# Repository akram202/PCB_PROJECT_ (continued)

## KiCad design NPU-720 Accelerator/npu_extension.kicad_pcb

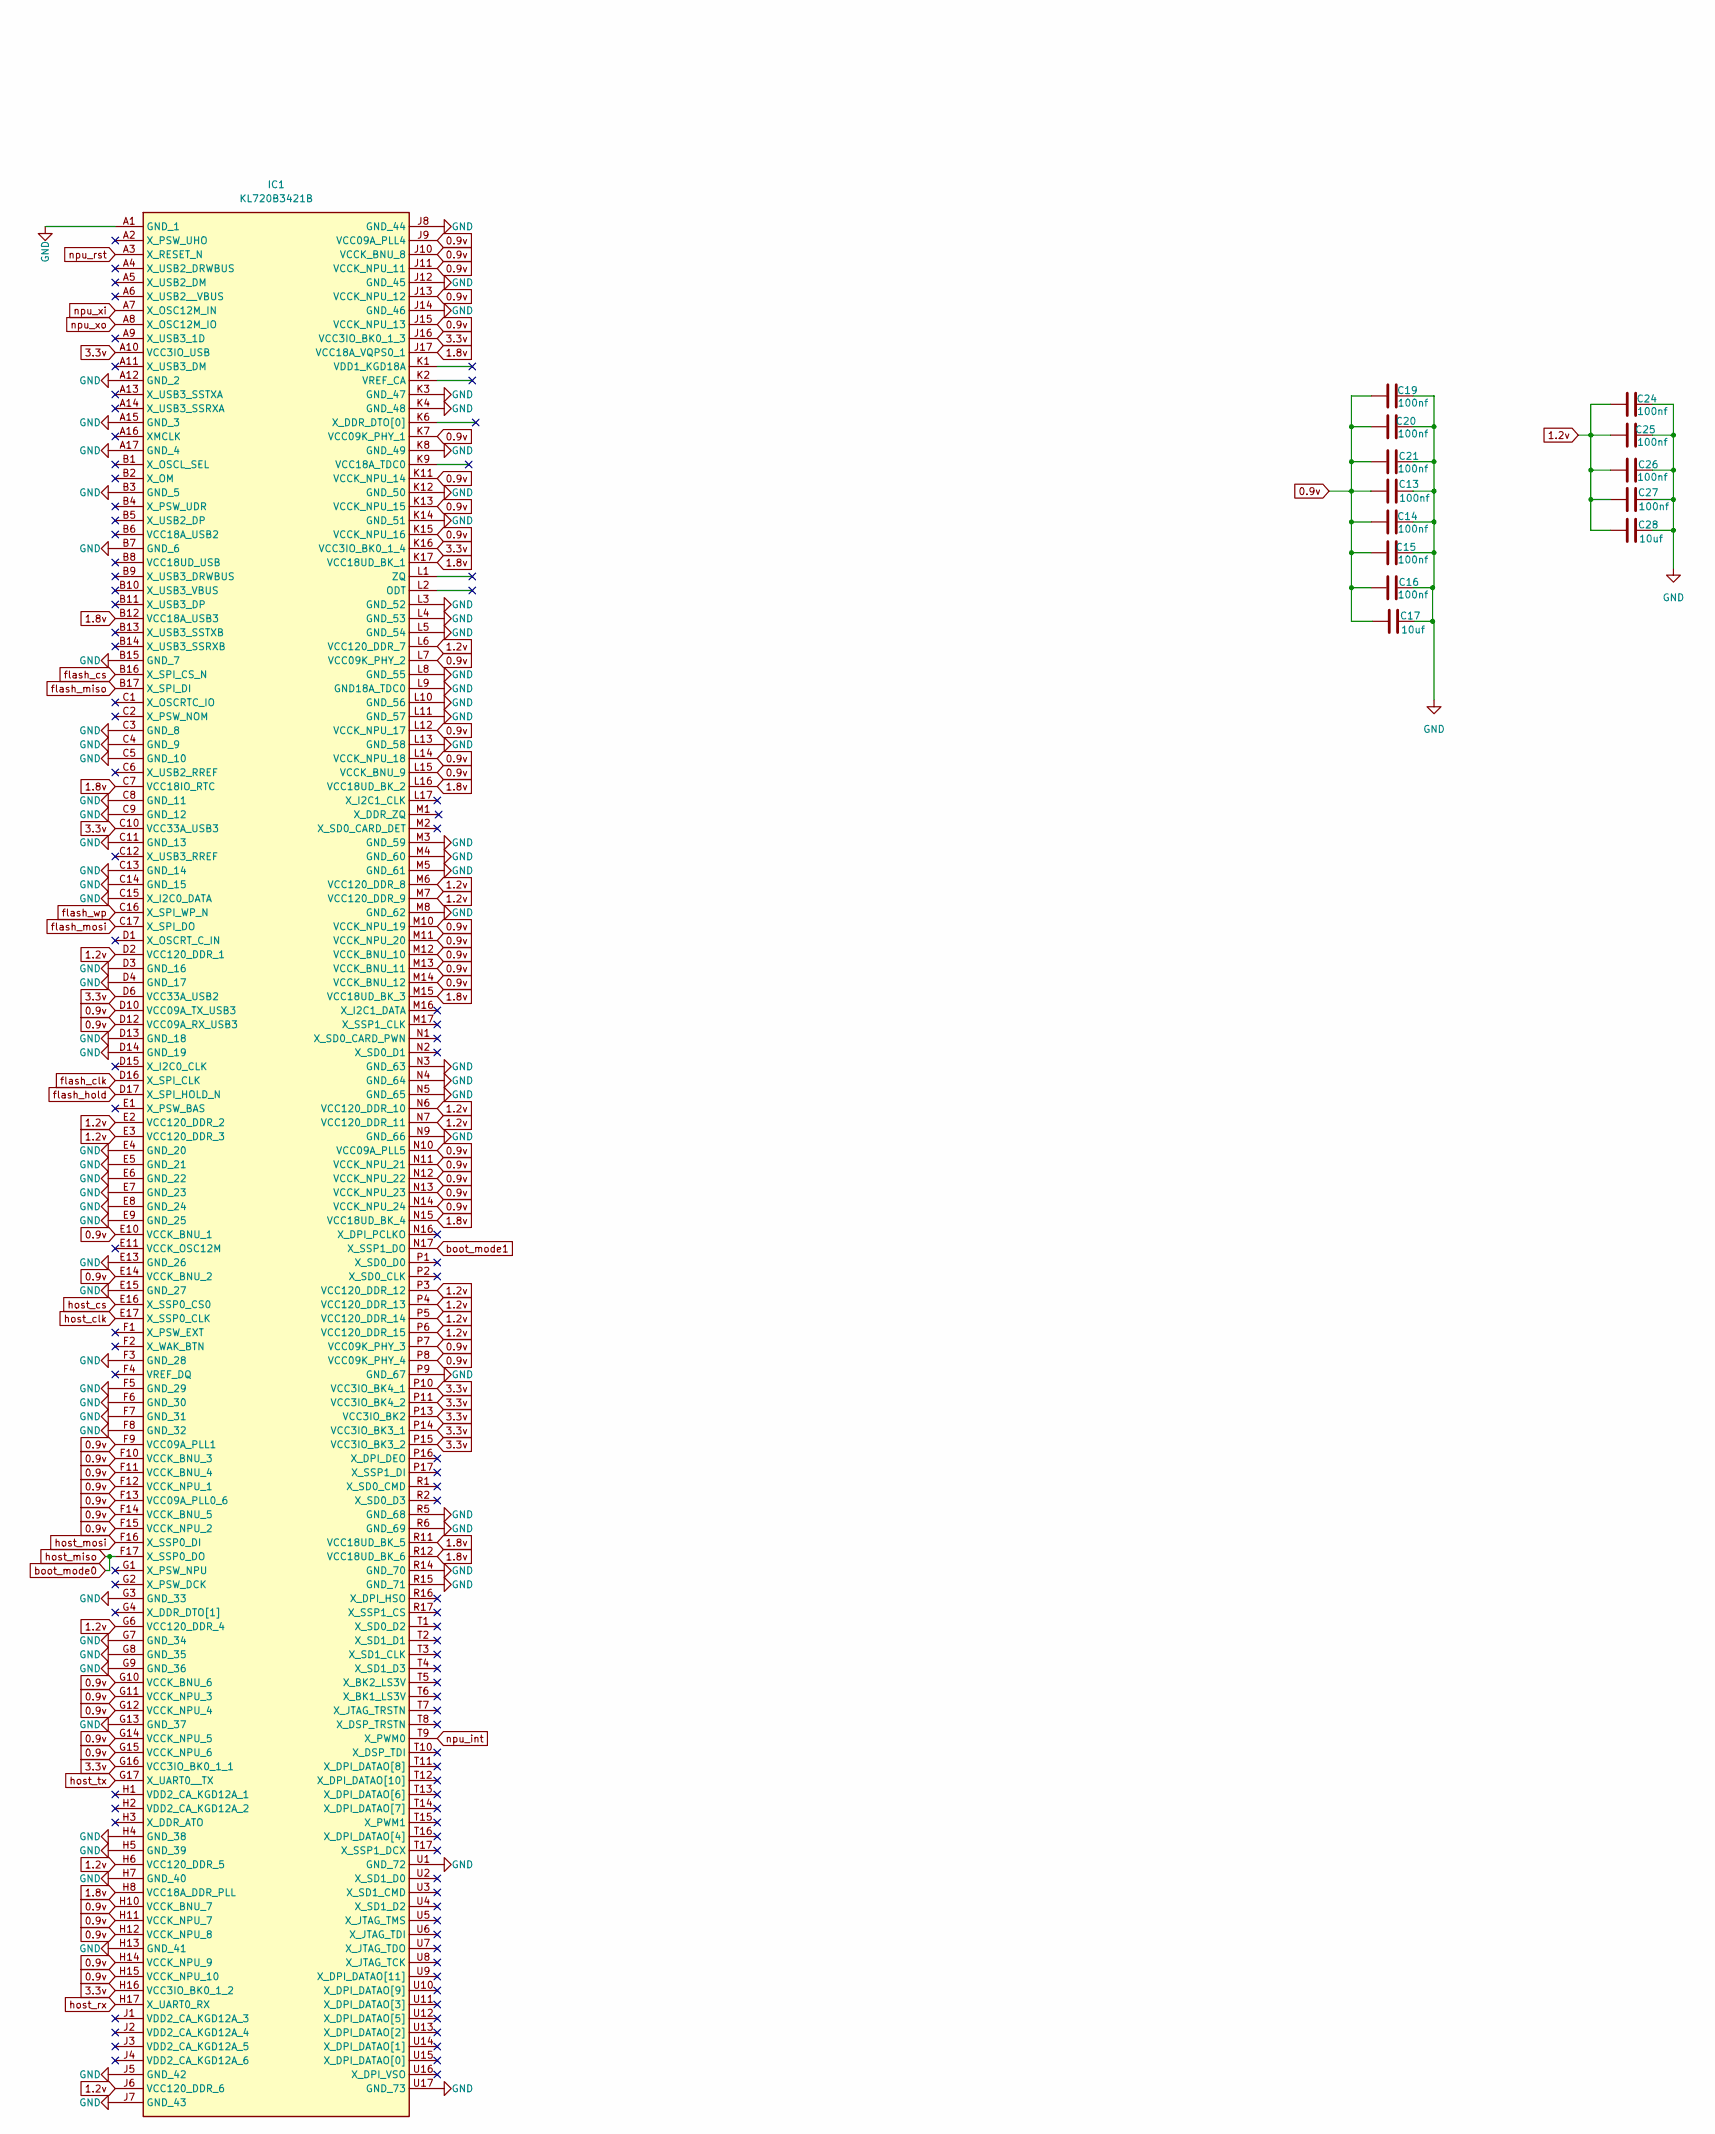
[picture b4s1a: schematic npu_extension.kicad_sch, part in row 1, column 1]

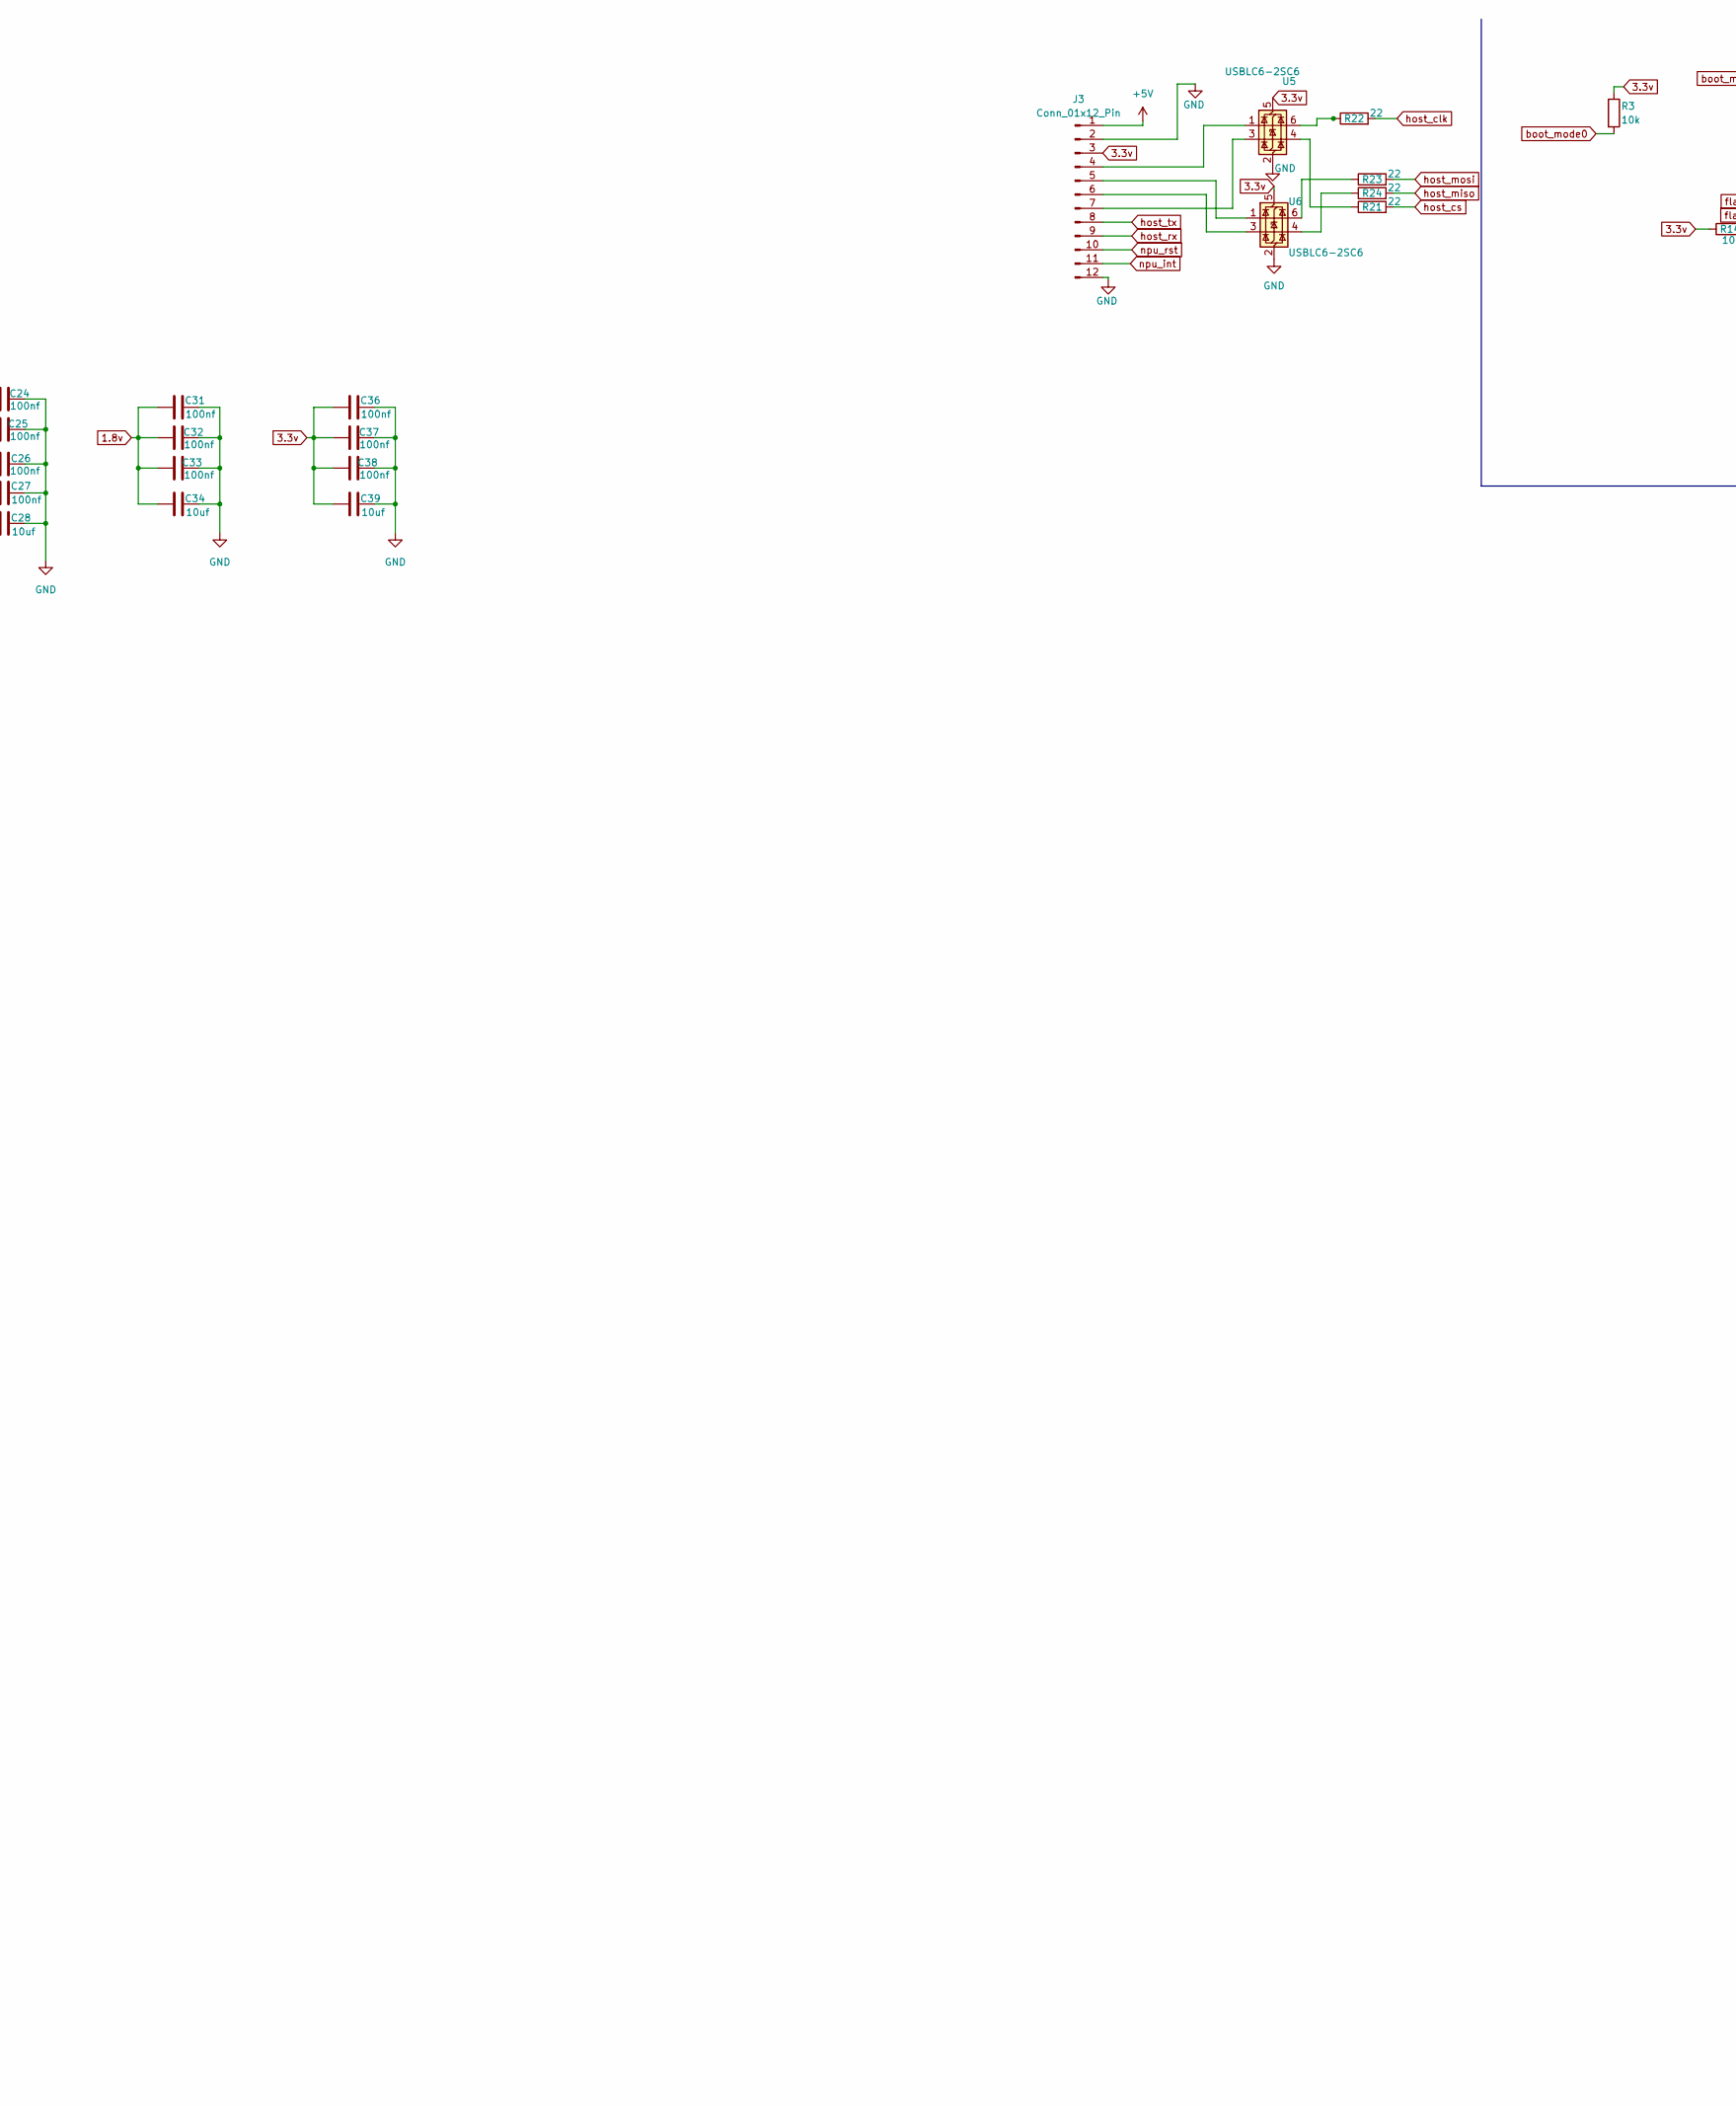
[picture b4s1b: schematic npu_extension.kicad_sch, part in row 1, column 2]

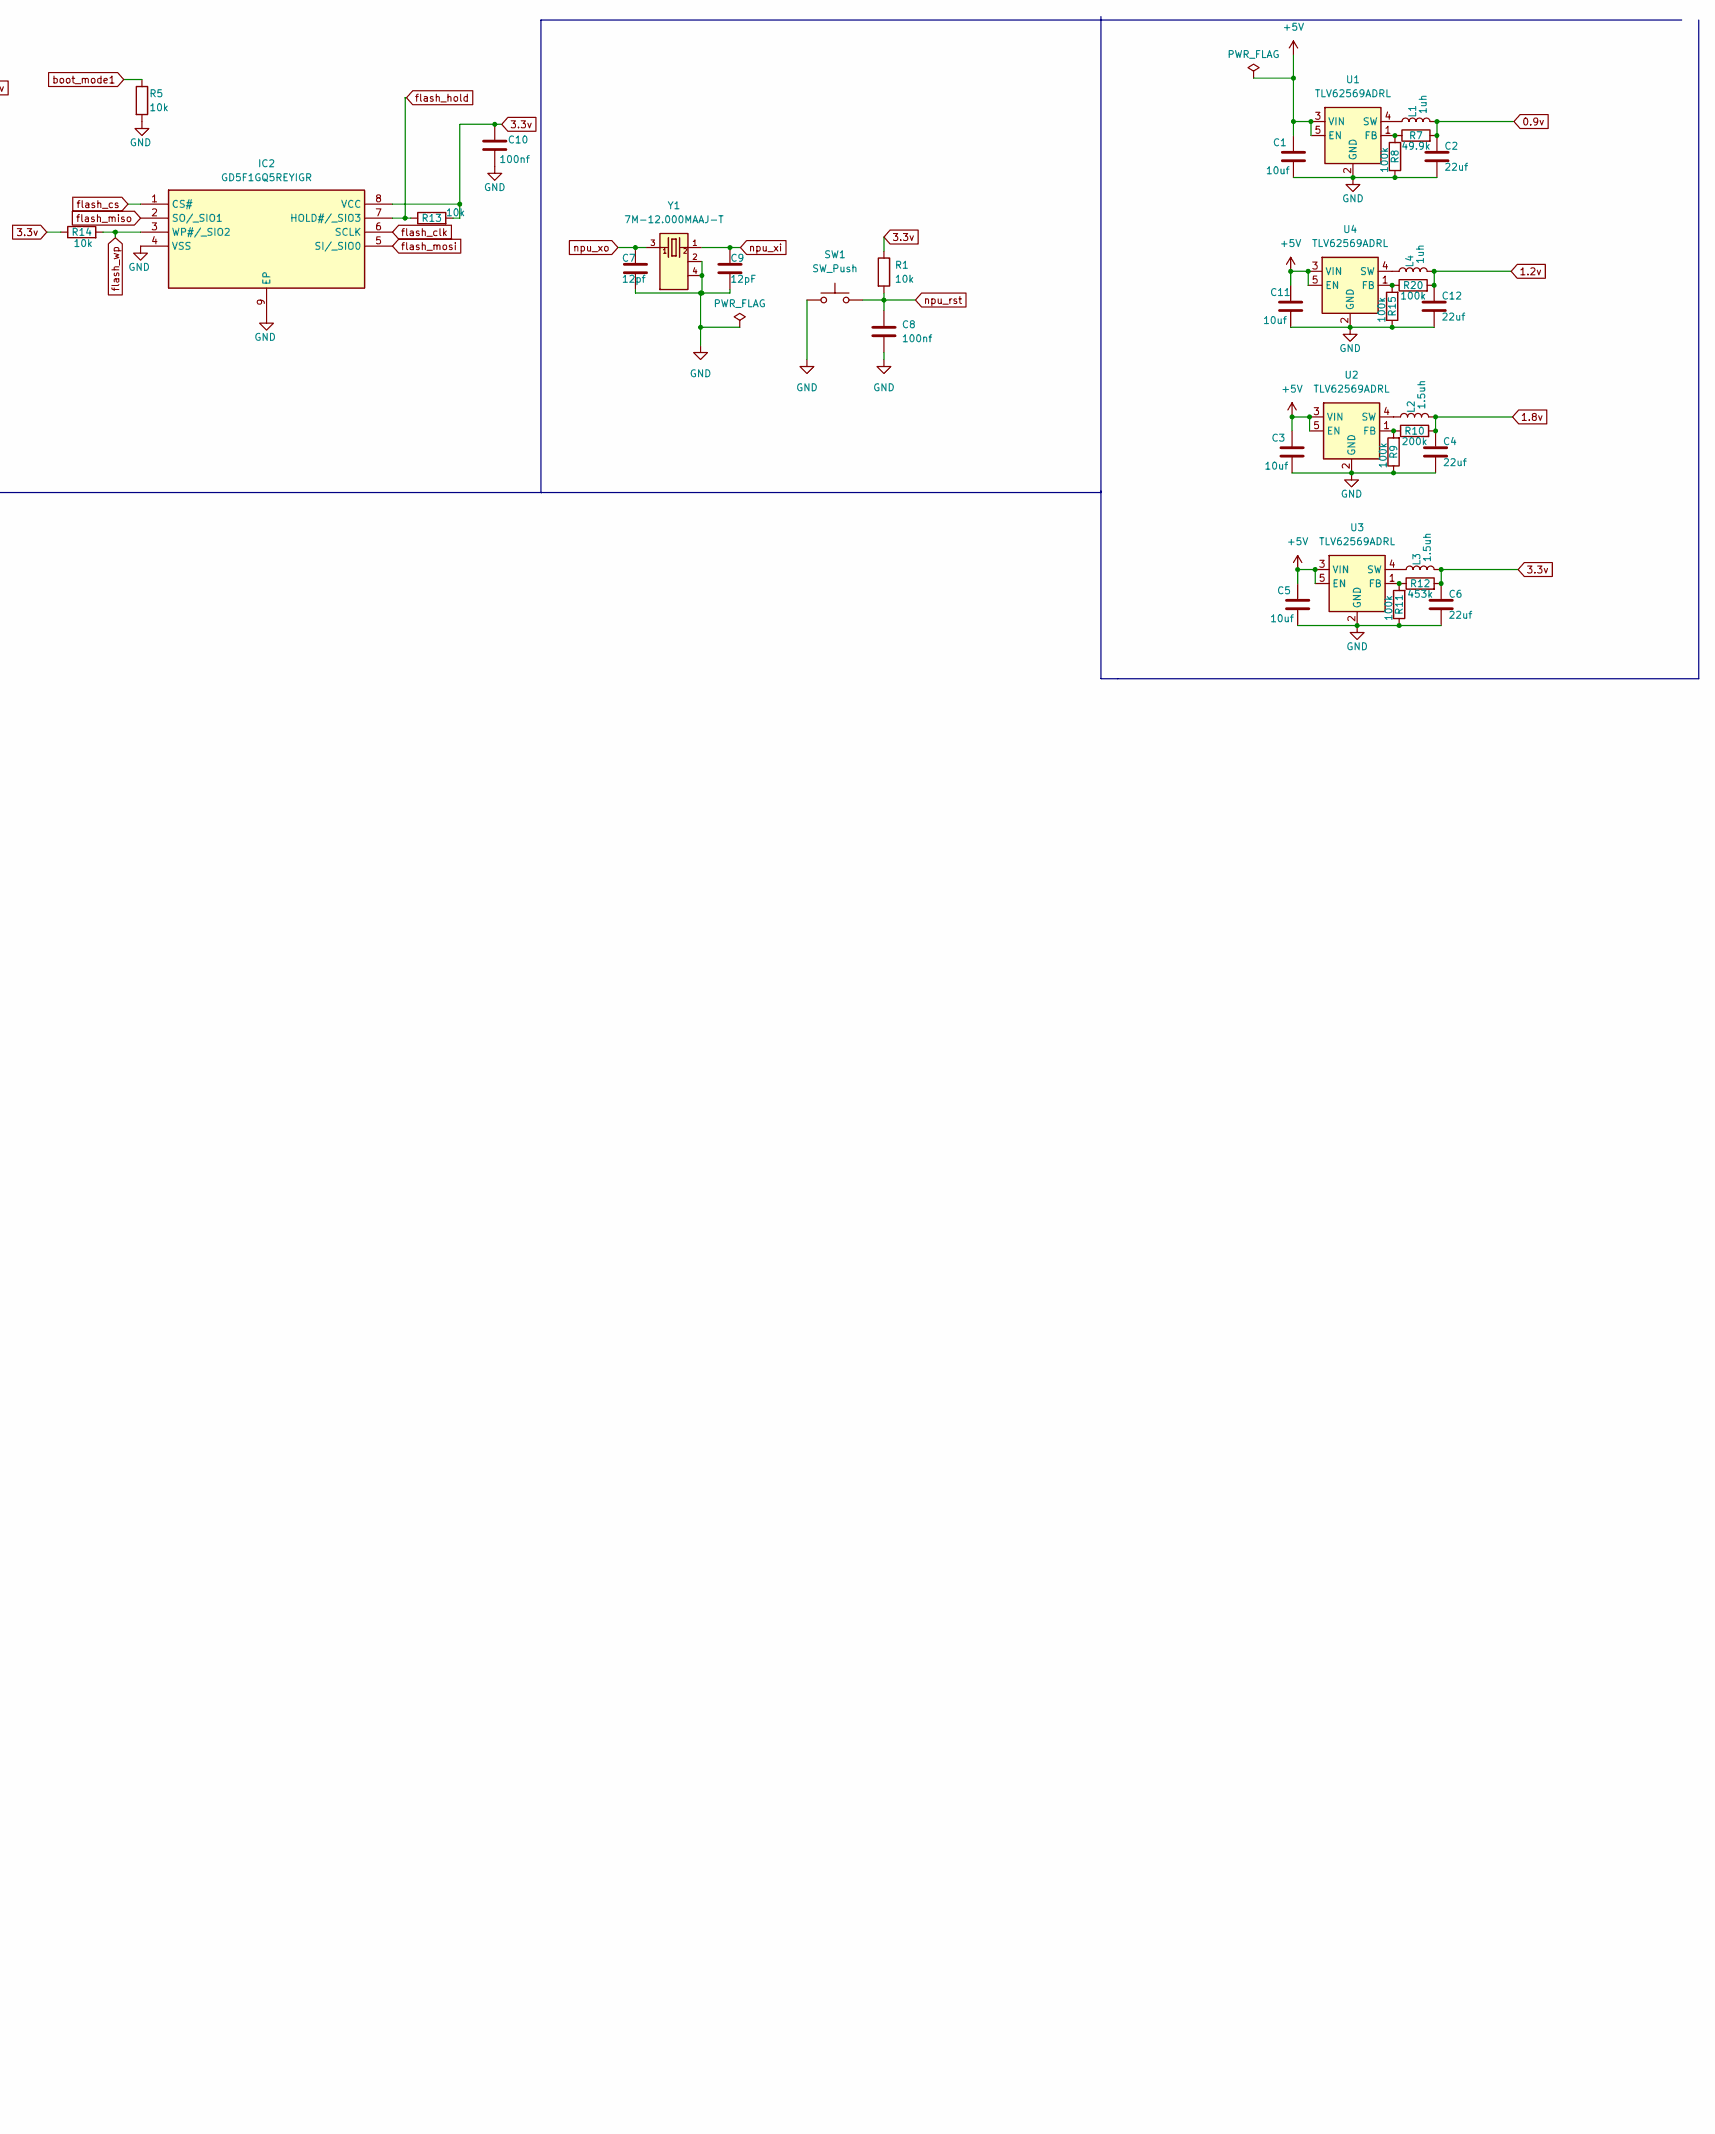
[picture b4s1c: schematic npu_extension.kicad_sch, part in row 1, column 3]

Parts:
C1, C3, C5, C11, C17, C28, C34, C39: 10uf; C_0805_2012Metric_Pad1.18x1.45mm_HandSolder
C2, C4, C6, C12: 22uf; C_0805_2012Metric_Pad1.18x1.45mm_HandSolder
C7: 12pf; C_0402_1005Metric_Pad0.74x0.62mm_HandSolder
C8, C10, C13, C14, C15, C16, C19, C20, C21, C24, C25, C26, C27, C31, C32, C33, C36, C37, C38: 100nf; C_0603_1608Metric_Pad1.08x0.95mm_HandSolder
C9: 12pF; C_0402_1005Metric_Pad0.74x0.62mm_HandSolder
IC1: KL720B3421B; BGA269C50P17X17_900X900X119; Manufacturer_Part_Number KL720B3421B; Mouser Part Number 827-KL720B3421B
IC2: GD5F1GQ5REYIGR; SON127P800X600X80-9N-D; Manufacturer_Part_Number GD5F1GQ5REYIGR
J3: Conn_01x12_Pin; JST_PH_S12B-PH-K_1x12_P2.00mm_Horizontal
L1, L4: 1uh; L_2512_6332Metric_Pad1.52x3.35mm_HandSolder
L2, L3: 1.5uh; L_2512_6332Metric_Pad1.52x3.35mm_HandSolder
R1, R3, R5, R13, R14: 10k; R_0603_1608Metric_Pad0.98x0.95mm_HandSolder
R7: 49.9k; R_0805_2012Metric_Pad1.20x1.40mm_HandSolder
R8, R9, R11, R15: 100k; R_0603_1608Metric_Pad0.98x0.95mm_HandSolder
R10: 200k; R_0805_2012Metric_Pad1.20x1.40mm_HandSolder
R12: 453k; R_0805_2012Metric_Pad1.20x1.40mm_HandSolder
R20: 100k; R_0805_2012Metric_Pad1.20x1.40mm_HandSolder
R21, R22, R23, R24: 22; R_0402_1005Metric_Pad0.72x0.64mm_HandSolder
SW1: SW_Push; SW_SPST_PTS645Sx43SMTR92
U1, U2, U3, U4: TLV62569ADRL; SOT-563
U5, U6: USBLC6-2SC6; SOT-23-6
Y1: 7M-12.000MAAJ-T; Crystal_SMD_2520-4Pin_2.5x2.0mm

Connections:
0.9v: C2.1, C13.1, C14.1, C15.1, C16.1, C17.1, C19.1, C20.1, C21.1, IC1.D10 (VCC09A_TX_USB3), IC1.D12 (VCC09A_RX_USB3), IC1.E10 (VCCK_BNU_1), IC1.E14 (VCCK_BNU_2), IC1.F9 (VCC09A_PLL1), IC1.F10 (VCCK_BNU_3), IC1.F11 (VCCK_BNU_4), IC1.F12 (VCCK_NPU_1), IC1.F13 (VCC09A_PLL0_6), IC1.F14 (VCCK_BNU_5), IC1.F15 (VCCK_NPU_2), IC1.G10 (VCCK_BNU_6), IC1.G11 (VCCK_NPU_3), IC1.G12 (VCCK_NPU_4), IC1.G14 (VCCK_NPU_5), IC1.G15 (VCCK_NPU_6), IC1.H10 (VCCK_BNU_7), IC1.H11 (VCCK_NPU_7), IC1.H12 (VCCK_NPU_8), IC1.H14 (VCCK_NPU_9), IC1.H15 (VCCK_NPU_10), IC1.J9 (VCC09A_PLL4), IC1.J10 (VCCK_BNU_8), IC1.J11 (VCCK_NPU_11), IC1.J13 (VCCK_NPU_12), IC1.J15 (VCCK_NPU_13), IC1.K7 (VCC09K_PHY_1), IC1.K11 (VCCK_NPU_14), IC1.K13 (VCCK_NPU_15), IC1.K15 (VCCK_NPU_16), IC1.L7 (VCC09K_PHY_2), IC1.L12 (VCCK_NPU_17), IC1.L14 (VCCK_NPU_18), IC1.L15 (VCCK_BNU_9), IC1.M10 (VCCK_NPU_19), IC1.M11 (VCCK_NPU_20), IC1.M12 (VCCK_BNU_10), IC1.M13 (VCCK_BNU_11), IC1.M14 (VCCK_BNU_12), IC1.N10 (VCC09A_PLL5), IC1.N11 (VCCK_NPU_21), IC1.N12 (VCCK_NPU_22), IC1.N13 (VCCK_NPU_23), IC1.N14 (VCCK_NPU_24), IC1.P7 (VCC09K_PHY_3), IC1.P8 (VCC09K_PHY_4), L1.2, R7.2; also elsewhere on the board
1.2v: C12.1, C24.1, C25.1, C26.1, C27.1, C28.1, IC1.D2 (VCC120_DDR_1), IC1.E2 (VCC120_DDR_2), IC1.E3 (VCC120_DDR_3), IC1.G6 (VCC120_DDR_4), IC1.H6 (VCC120_DDR_5), IC1.J6 (VCC120_DDR_6), IC1.L6 (VCC120_DDR_7), IC1.M6 (VCC120_DDR_8), IC1.M7 (VCC120_DDR_9), IC1.N6 (VCC120_DDR_10), IC1.N7 (VCC120_DDR_11), IC1.P3 (VCC120_DDR_12), IC1.P4 (VCC120_DDR_13), IC1.P5 (VCC120_DDR_14), IC1.P6 (VCC120_DDR_15), L4.2, R20.2; also elsewhere on the board
1.8v: C4.1, C31.1, C32.1, C33.1, C34.1, IC1.B12 (VCC18A_USB3), IC1.C7 (VCC18IO_RTC), IC1.H8 (VCC18A_DDR_PLL), IC1.J17 (VCC18A_VQPS0_1), IC1.K17 (VCC18UD_BK_1), IC1.L16 (VCC18UD_BK_2), IC1.M15 (VCC18UD_BK_3), IC1.N15 (VCC18UD_BK_4), IC1.R11 (VCC18UD_BK_5), IC1.R12 (VCC18UD_BK_6), L2.2, R10.2; also elsewhere on the board
3.3v: C6.1, C10.1, C36.1, C37.1, C38.1, C39.1, IC1.A10 (VCC3IO_USB), IC1.C10 (VCC33A_USB3), IC1.D6 (VCC33A_USB2), IC1.G16 (VCC3IO_BK0_1_1), IC1.H16 (VCC3IO_BK0_1_2), IC1.J16 (VCC3IO_BK0_1_3), IC1.K16 (VCC3IO_BK0_1_4), IC1.P10 (VCC3IO_BK4_1), IC1.P11 (VCC3IO_BK4_2), IC1.P13 (VCC3IO_BK2), IC1.P14 (VCC3IO_BK3_1), IC1.P15 (VCC3IO_BK3_2), IC2.8 (VCC), J3.3, L3.2, R1.1, R3.1, R12.2, R13.2, R14.1, U5.5 (VBUS), U6.5 (VBUS); also elsewhere on the board
+5V: C1.1, C3.1, C5.1, C11.1, J3.1, U1.3 (VIN), U1.5 (EN), U2.3 (VIN), U2.5 (EN), U3.3 (VIN), U3.5 (EN), U4.3 (VIN), U4.5 (EN)
GND: C1.2, C2.2, C3.2, C4.2, C5.2, C6.2, C7.2, C8.2, C9.2, C10.2, C11.2, C12.2, C13.2, C14.2, C15.2, C16.2, C17.2, C19.2, C20.2, C21.2, C24.2, C25.2, C26.2, C27.2, C28.2, C31.2, C32.2, C33.2, C34.2, C36.2, C37.2, C38.2, C39.2, IC1.A1 (GND_1), IC1.A12 (GND_2), IC1.A15 (GND_3), IC1.A17 (GND_4), IC1.B3 (GND_5), IC1.B7 (GND_6), IC1.B15 (GND_7), IC1.C3 (GND_8), IC1.C4 (GND_9), IC1.C5 (GND_10), IC1.C8 (GND_11), IC1.C9 (GND_12), IC1.C11 (GND_13), IC1.C13 (GND_14), IC1.C14 (GND_15), IC1.C15 (X_I2C0_DATA), IC1.D3 (GND_16), IC1.D4 (GND_17), IC1.D13 (GND_18), IC1.D14 (GND_19), IC1.E4 (GND_20), IC1.E5 (GND_21), IC1.E6 (GND_22), IC1.E7 (GND_23), IC1.E8 (GND_24), IC1.E9 (GND_25), IC1.E13 (GND_26), IC1.E15 (GND_27), IC1.F3 (GND_28), IC1.F5 (GND_29), IC1.F6 (GND_30), IC1.F7 (GND_31), IC1.F8 (GND_32), IC1.G3 (GND_33), IC1.G7 (GND_34), IC1.G8 (GND_35), IC1.G9 (GND_36), IC1.G13 (GND_37), IC1.H4 (GND_38), IC1.H5 (GND_39), IC1.H7 (GND_40), IC1.H13 (GND_41), IC1.J5 (GND_42), IC1.J7 (GND_43), IC1.J8 (GND_44), IC1.J12 (GND_45), IC1.J14 (GND_46), IC1.K3 (GND_47), IC1.K4 (GND_48), IC1.K8 (GND_49), IC1.K12 (GND_50), IC1.K14 (GND_51), IC1.L3 (GND_52), IC1.L4 (GND_53), IC1.L5 (GND_54), IC1.L8 (GND_55), IC1.L9 (GND18A_TDC0), IC1.L10 (GND_56), IC1.L11 (GND_57), IC1.L13 (GND_58), IC1.M3 (GND_59), IC1.M4 (GND_60), IC1.M5 (GND_61), IC1.M8 (GND_62), IC1.N3 (GND_63), IC1.N4 (GND_64), IC1.N5 (GND_65), IC1.N9 (GND_66), IC1.P9 (GND_67), IC1.R5 (GND_68), IC1.R6 (GND_69), IC1.R14 (GND_70), IC1.R15 (GND_71), IC1.U1 (GND_72), IC1.U17 (GND_73), IC2.4 (VSS), IC2.9 (EP), J3.2, J3.12, R5.2, R8.1, R9.1, R11.1, R15.1, SW1.1, U1.2 (GND), U2.2 (GND), U3.2 (GND), U4.2 (GND), U5.2 (GND), U6.2 (GND), Y1.2, Y1.4; also elsewhere on the board
unnamed: J3.4, U5.1 (I/O1)
unnamed: J3.5, U6.1 (I/O1)
unnamed: J3.6, U6.3 (I/O2)
unnamed: J3.7, U5.3 (I/O2)
unnamed: R21.1, U5.4 (I/O2)
unnamed: R22.1, U5.6 (I/O1)
unnamed: R23.1, U6.6 (I/O1)
unnamed: R24.1, U6.4 (I/O2)
unnamed: R7.1, R8.2, U1.1 (FB)
unnamed: L1.1, U1.4 (SW)
unnamed: R9.2, R10.1, U2.1 (FB)
unnamed: L2.1, U2.4 (SW)
unnamed: R11.2, R12.1, U3.1 (FB)
unnamed: L3.1, U3.4 (SW)
unnamed: R15.2, R20.1, U4.1 (FB)
unnamed: L4.1, U4.4 (SW)
boot_mode0: IC1.F17 (X_SSP0_DO), R3.2, R24.2
boot_mode1: IC1.N17 (X_SSP1_DO), R5.1
flash_clk: IC1.D16 (X_SPI_CLK), IC2.6 (SCLK)
flash_cs: IC1.B16 (X_SPI_CS_N), IC2.1 (CS#)
flash_hold: IC1.D17 (X_SPI_HOLD_N), IC2.7 (HOLD#/_SIO3), R13.1
flash_miso: IC1.B17 (X_SPI_DI), IC2.2 (SO/_SIO1)
flash_mosi: IC1.C17 (X_SPI_DO), IC2.5 (SI/_SIO0)
flash_wp: IC1.C16 (X_SPI_WP_N), IC2.3 (WP#/_SIO2), R14.2
host_clk: IC1.E17 (X_SSP0_CLK), R22.2
host_cs: IC1.E16 (X_SSP0_CS0), R21.2
host_mosi: IC1.F16 (X_SSP0_DI), R23.2
host_rx: IC1.H17 (X_UART0_RX), J3.9
host_tx: IC1.G17 (X_UART0__TX), J3.8
npu_int: IC1.T9 (X_PWM0), J3.11
npu_rst: C8.1, IC1.A3 (X_RESET_N), J3.10, R1.2, SW1.2
npu_xi: C9.1, IC1.A7 (X_OSC12M_IN), Y1.1
npu_xo: C7.1, IC1.A8 (X_OSC12M_IO), Y1.3

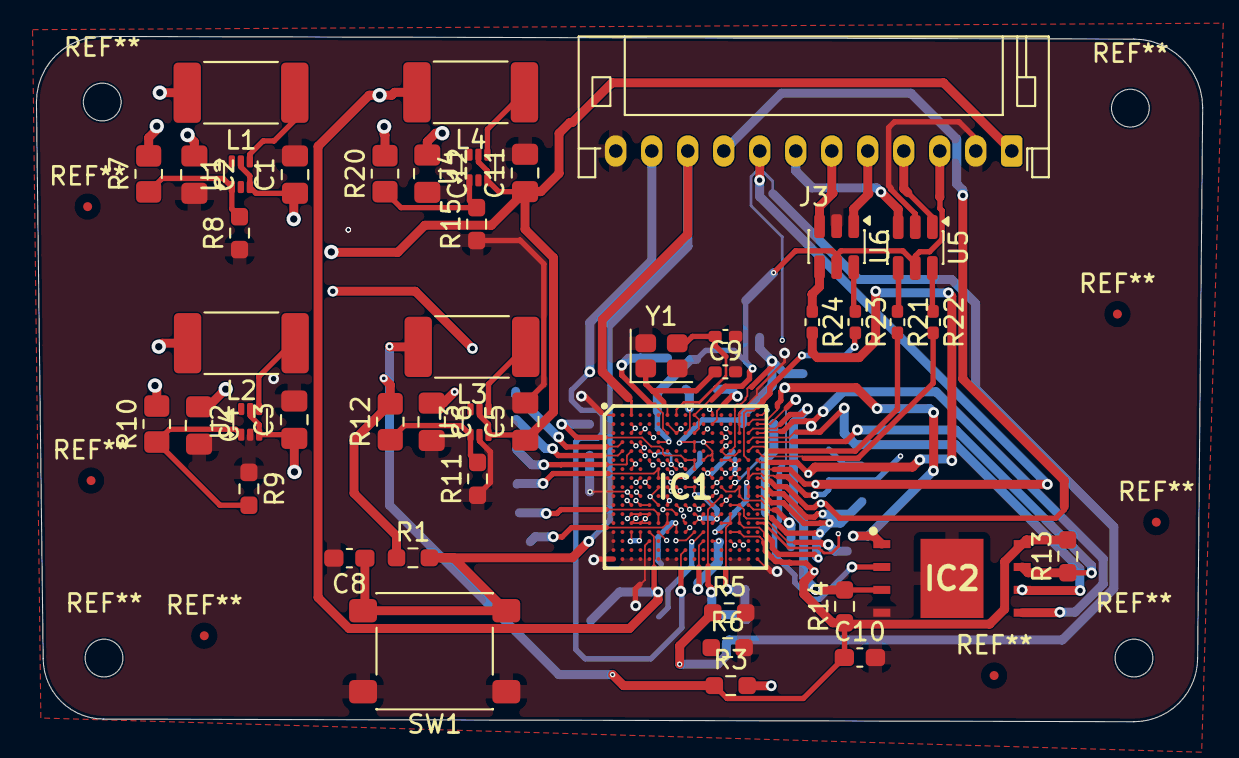
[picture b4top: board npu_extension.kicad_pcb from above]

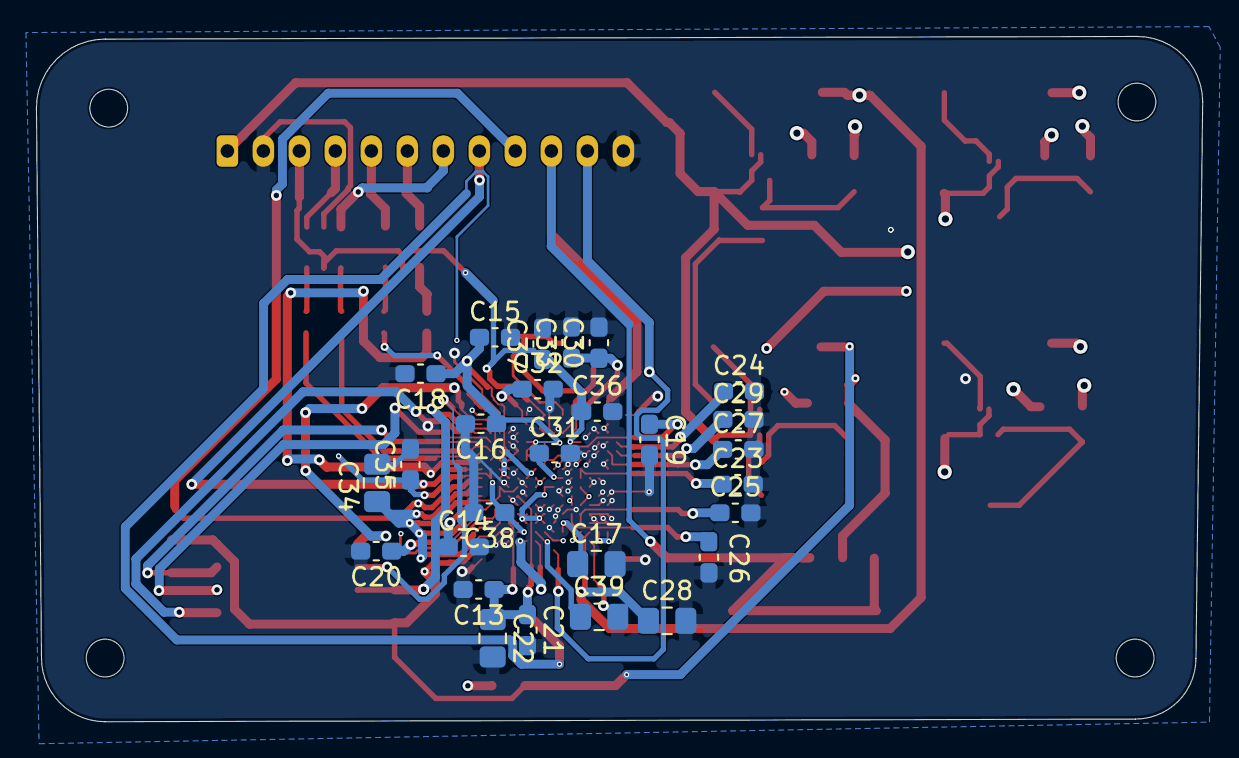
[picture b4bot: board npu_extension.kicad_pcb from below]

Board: 4 copper layers, 64.8 x 38.1 mm, 72 parts (27 on the bottom side), 39 nets.

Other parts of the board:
C18, C23, C29, C30, C35: 100nf; C_0603_1608Metric_Pad1.08x0.95mm_HandSolder
C22: 10uf; C_0805_2012Metric_Pad1.18x1.45mm_HandSolder
R6: 10k; R_0603_1608Metric_Pad0.98x0.95mm_HandSolder

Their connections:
0.9v: C18.1, C22.1; also elsewhere on the board
1.2v: C23.1, C29.1; also elsewhere on the board
1.8v: C30.1; also elsewhere on the board
3.3v: C35.1; also elsewhere on the board
GND: C18.2, C22.2, C23.2, C29.2, C30.2, C35.2, R6.2; also elsewhere on the board

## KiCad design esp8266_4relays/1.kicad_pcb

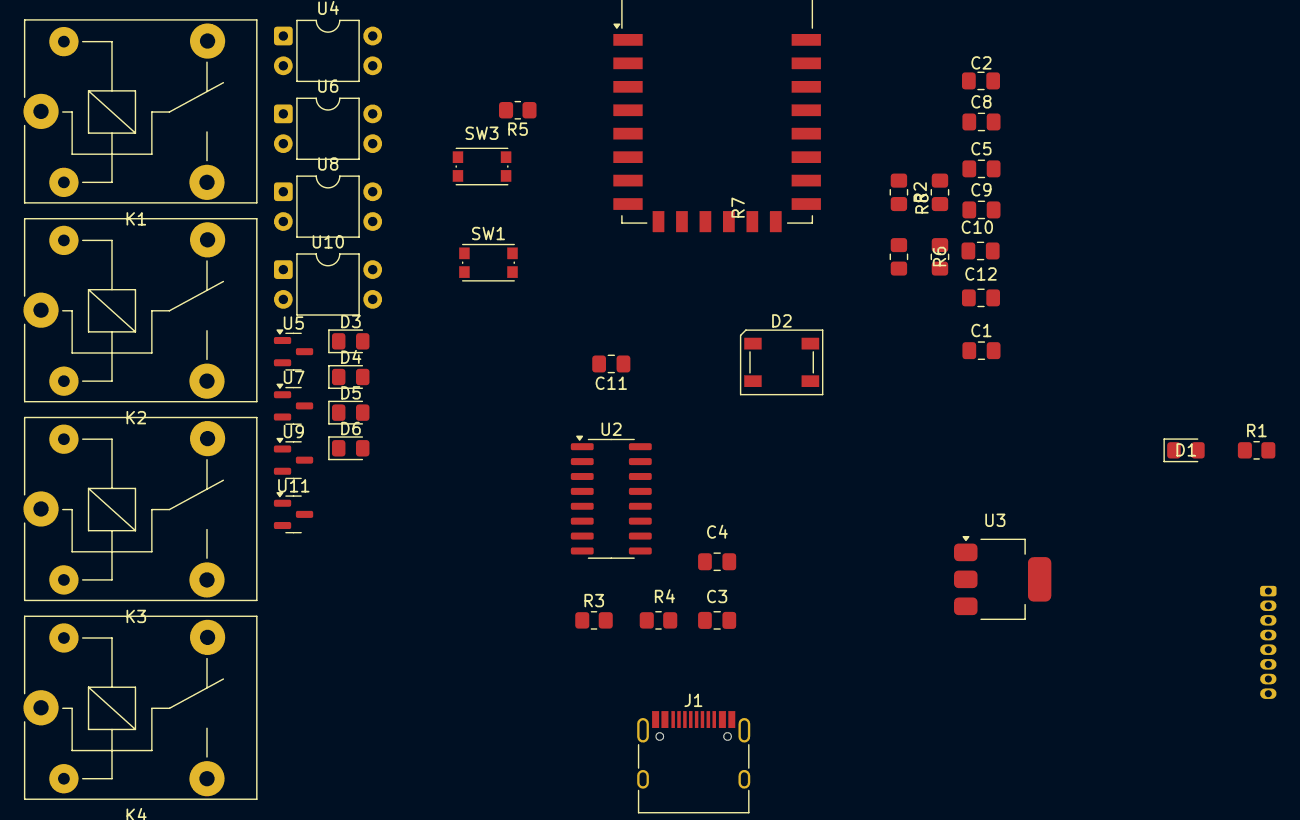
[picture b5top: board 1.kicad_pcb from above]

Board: 2 copper layers, 43 parts (1 on the bottom side), 33 nets, no tracks yet.

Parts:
C1, C5, C8, C9, C10, C11, C12: 0.1uF; C_0805_2012Metric_Pad1.18x1.45mm_HandSolder
C2, C4: 0u1F; C_0805_2012Metric_Pad1.18x1.45mm_HandSolder
C3: 22uF; C_0805_2012Metric_Pad1.18x1.45mm_HandSolder
D1, D3, D4, D5, D6: LED; LED_0805_2012Metric_Pad1.15x1.40mm_HandSolder
D2: SK6812; LED_SK6812_PLCC4_5.0x5.0mm_P3.2mm
J1: USB_C_Receptacle_USB2.0_14P; USB_C_Receptacle_HRO_TYPE-C-31-M-12
J3: Conn_01x08; Hirose_DF13-08P-1.25DSA_1x08_P1.25mm_Vertical
K1, K2, K3, K4: SANYOU_SRD_Form_C; Relay_SPDT_SANYOU_SRD_Series_Form_C
R1: 680; R_0805_2012Metric_Pad1.20x1.40mm_HandSolder
R2, R5, R6, R7, R8: 10k; R_0805_2012Metric_Pad1.20x1.40mm_HandSolder
R3, R4: 5.1K; R_0805_2012Metric_Pad1.20x1.40mm_HandSolder
SW1, SW3: KMR211GLFS; SW_Push_1P1T_NO_CK_KMR2
U1: ESP-12F; ESP-12E
U2: CH340C; SOIC-16_3.9x9.9mm_P1.27mm
U3: AMS1117-3.3; SOT-223-3_TabPin2
U4, U6, U8, U10: PC817; DIP-4_W7.62mm
U5, U7, U9, U11: IRLML2502TRPBF; SOT-23

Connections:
3v3 VCC: C1.1, C2.1, C12.1, D1.2 (A), D2.3 (VDD), J3.1, R2.1, R5.1, R6.1, R7.1, U1.8 (VCC), U2.16 (VCC), U3.2 (VO)
5v VCC: C3.1, C4.1, K1.3, K1.5, K2.3, K2.5, K3.3, K3.5, K4.3, K4.5, U3.3 (VI)
BL: C9.1, C10.1, J3.8, R6.2, SW1.2, U1.18 (GPIO0)
CS: J3.5, U1.9 (CS0)
D+: J1.B6 (D+), U2.5 (UD+)
D-: J1.B7 (D-), U2.6 (UD-)
DTR: C10.2, U2.13 (~DTR)
GND: C1.2, C2.2, C3.2, C4.2, C5.2, C8.2, C9.2, C12.2, D2.1 (VSS), J1.A1 (GND), J1.A12 (GND), J1.B1 (GND), J1.B12 (GND), J1.S1 (SHIELD), J3.2, R1.2, R3.2, R4.2, R8.2, SW1.1, SW3.1, U1.15 (GND), U2.1 (GND), U3.1 (GND), U4.2, U5.2, U6.2, U7.2, U8.2, U9.2, U10.2, U11.2
MISO: J3.4, U1.10 (MISO)
MOSI: J3.3, U1.13 (MOSI)
unnamed: D1.1 (K), R1.1
unnamed: D3.2 (A), K1.1
unnamed: D4.2 (A), K2.1
unnamed: D5.2 (A), K3.1
unnamed: D6.2 (A), K4.1
unnamed: J1.A4 (VBUS), J1.A9 (VBUS), J1.B4 (VBUS), J1.B9 (VBUS)
unnamed: K1.2, U5.3
unnamed: K2.2, U7.3
unnamed: K3.2, U9.3
unnamed: K4.2, U11.3
unnamed: U4.3, U5.1
unnamed: U6.3, U7.1
unnamed: U8.3, U9.1
unnamed: U10.3, U11.1
unnamed: R7.2, U1.17 (GPIO2)
unnamed: R8.1, U1.16 (GPIO15)
RST: C11.2, J3.7, U1.1 (~RST)
RTS: C11.1, U2.14 (~RTS)
RX: U1.21 (GPIO3/RXD), U2.3 (RXD)
TX: U1.22 (GPIO1/TXD), U2.2 (TXD)
cc1: J1.A5 (CC1), R3.1
cc2: J1.B5 (CC2), R4.1
chip_pu: C5.1, C8.1, R2.2, R5.2, SW3.2, U1.3 (EN)
